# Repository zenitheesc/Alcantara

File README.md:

<h1 align="center" style="color:white; background-color:black">Alcantara</h1>
<h4 align="center"> Mobile Ground Station for stratospheric probe monitoring and rescue</h4>

<p align="center">

</p>

<p align="center">
    <a href="#environment-and-tools">Environment and Tools</a> •
    <a href="#Block-Diagram">Block Diagram</a> •
    <a href="#Schematic">Schematic</a> • 
    <a href="#Board">Board</a> • 
    <a href="#BOM">BOM</a> • 
    <a href="#Use-Concept">Use Concept</a>
</p>

The Alcantara board functions as a ground station and data hub for the probe flights .

It is equipped with a EBYTE E22-900M30S 30dB module that carries the Semtech SX1262 transceiver, capable of LoRa, (G)FSK and OOK. The packets received from the probe can then be sent via WiFi, Bluetooth or Serially to a host computer or mobile phone.

The onboard GNSS module carries the NEO-M8N from u-blox, enabling it to be used as a tracking device.

## Environment and tools

This system was designed using KiCad 5.1.10.

## Block Diagram

## Schematic

The design was separated in hierarchical sheets to accommodate all components in an orderly way.

On the experimental_realocate_components sheet you can find the ESP32 WROOM Module, the SD Card module (connected via SPI), Boot and Reset button (with the Brownout prevention voltage supervisor), auto upload transistors and the external connector.

The second page contains the power section, with the TPS61092 Boost Converter (with another voltage supervisor for undervolting protection for the battery) for 5V, a 3.3V linear voltage regulator, the battery with a P channel mosfet for reverse voltage protection and a MAX17201G+T stand-alone fuel gauge for the 18650 battery voltage and current monitoring.

On the third page you find the Neo-M8N module from u-blox and the E22-900M30S module from EBYTE.

And the last page has the peripherals, the USB connector with its ESD protector, the RGB LED, the buzzer with its mosfet, the two user interface buttons and the USB to Serial Converter.

## Board

## Interactive BOM

https://htmlpreview.github.io/?https://github.com/zenitheesc/Alcantara_v.1.0/blob/experimental_realocate_components/Other_Files/ibom.html

<!--
## Use concept

---

<p align="center">

</p>
<p align = "center">
<a href="zenith.eesc@gmail.com">zenith.eesc@gmail.com</a>
</p>
-->

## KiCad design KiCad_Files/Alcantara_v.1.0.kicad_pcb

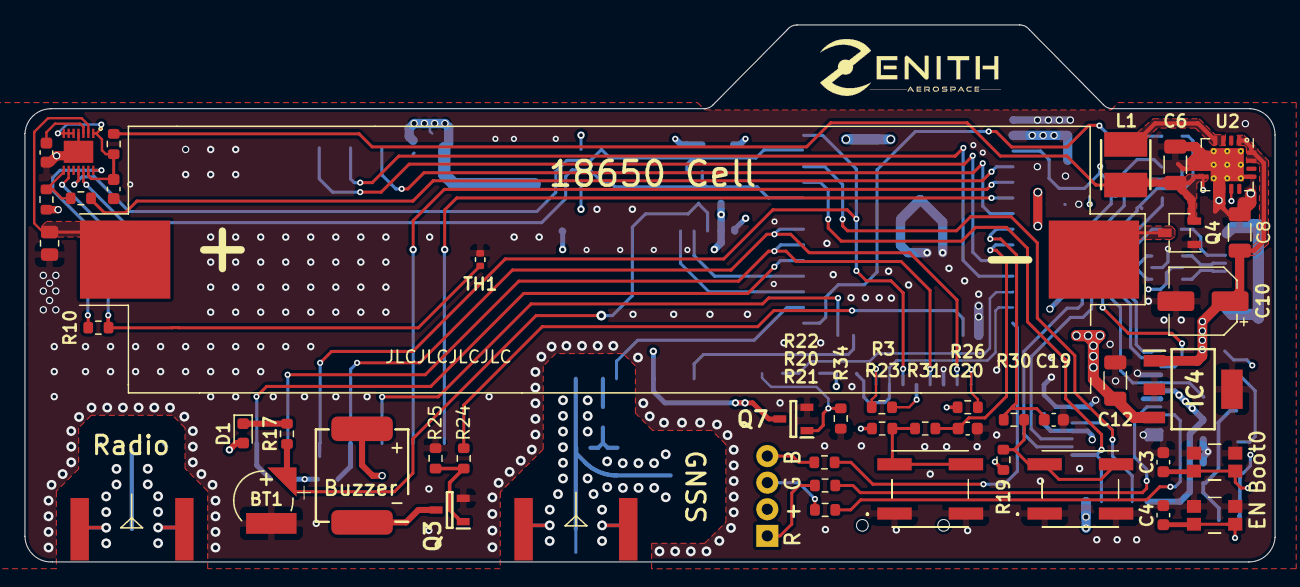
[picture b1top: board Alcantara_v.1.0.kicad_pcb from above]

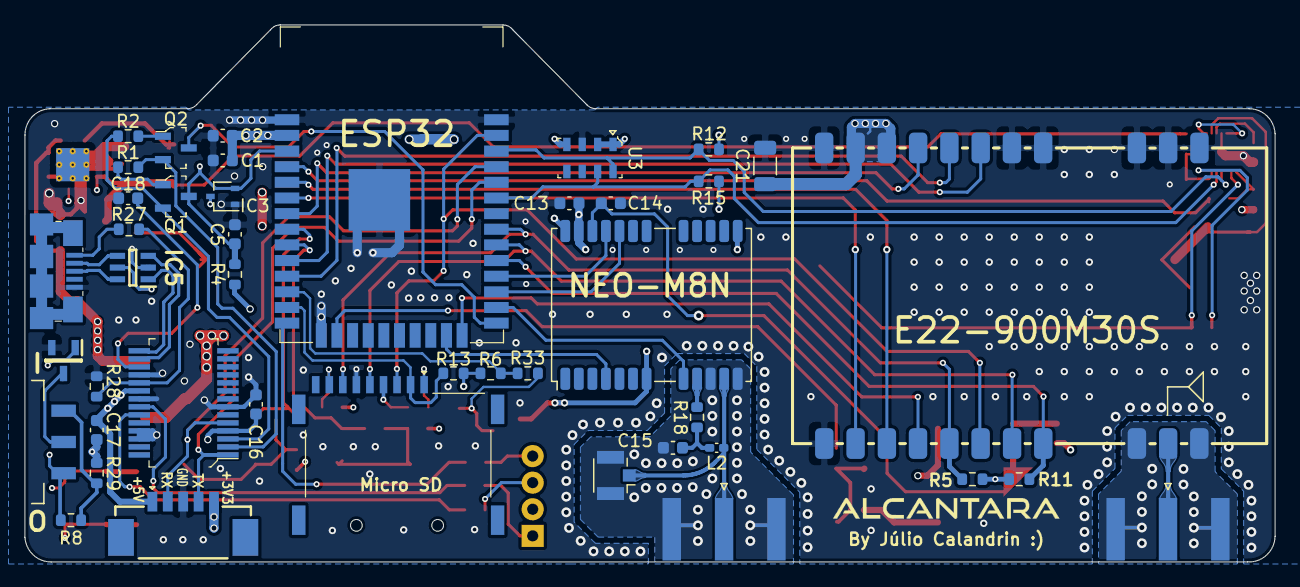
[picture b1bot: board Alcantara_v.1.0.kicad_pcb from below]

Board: 4 copper layers, 101.5 x 43.6 mm, 88 parts (43 on the bottom side), 74 nets.

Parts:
BT1: ML414H_IV01E; SEIKO_ML414H_IV01E
BT2: Battery_Cell; BatteryHolder_Keystone_1042_1x18650_Modified
C1, C3, C4, C9: 0.1uF; C_0603_1608Metric
C2, C5: 10uF; C_0603_1608Metric
C6, C12: 10uF; C_1206_3216Metric
C7: 0.47uF; C_0603_1608Metric
C8: 2.2uF; C_1206_3216Metric
C10: 100uF; CP_Elec_5x5.3
C13, C14, C19, C20: 1uF; C_0603_1608Metric
C15: 10nF; C_0603_1608Metric
C16, C17, C18: 100nF; C_0603_1608Metric
C21: 1uF; C_1206_3216Metric
D1: D_Schottky_Small; D_0603_1608Metric
D2: LED_RGBA; LED_D5.0mm-4_RGB_Wide_Pins
IC1: TLV809ED29DBZR; SOT95P237X112-3N
IC2: MAX17201G+T; SON40P300X300X80-15N
IC3: TLV803EA30DCKR; SOT-323_SC-70
IC4: TC1264-3.3VDB; SOT230P700X180-4N
IC5: PESD2ETH-ADX; SOT95P275X110-6N
J1: U_FL-R-SMT_10_; U.FL_Hirose_U.FL-R-SMT-1_Vertical
J2, J3: 142-0701-801; SMA_Amphenol_132289_EdgeMount
J4: USB_B_Micro; USB_Micro_B_Female_10118192
J5: MEM2075-00-140-01-A; MEM20750014001A
J8: 53261-0527; 532610527
L1: 6.8uH; INDPM4040X210N
L2: L_Small; L_0402_1005Metric_Pad0.77x0.64mm_HandSolder
MOD1: ESP32-WROOM-32; ESP32-WROOM-32D
Q1, Q2: MMSS8050-H-TP; SOT-23-3
Q3, Q7: 2N7002NXAKR; SOT95P230X110-3N
Q4: Q_PMOS_GSD; SOT346
R1, R2, R3, R4, R5, R6, R10, R11, R13, R19, R23, R25, R26, R28, R34: 10K; R_0603_1608Metric
R7: 0.01; R_0805_2012Metric
R8: 68k; R_0603_1608Metric
R9, R18: 10; R_0603_1608Metric
R12, R14, R15, R27: 4.7K; R_0603_1608Metric
R16, R20, R21, R22, R30, R31: 1K; R_0603_1608Metric
R17: 3.3K; R_0603_1608Metric
R24, R33: 330; R_0603_1608Metric
R29: 100k; R_0603_1608Metric
S1, S2: KSC941JLFS
S4, S5: EVP-AAM02W; EVPAAM02W
S6: MSS-102545-14A-V-SMT; SW_MSS-102545-14A-V-SMT
TH1: 10k; R_0402_1005Metric
U1: E22-900M30S
U2: TPS61092; Texas_S-PVQFN-N16_EP2.7x2.7mm_ThermalVias
U3: MS560702BA03-50; SMD-8_5x3mm
U4: NEO-M8N; ublox_NEO
U5: Buzzer_SMD_AST0760MCTRQ; AST0760MCTRQ
U7: FT232RL-REEL; SSOP-28_W5.30mm

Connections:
+3V3: C1.1, C2.1, C12.1, C13.1, C16.1, D1.2, D2.4, IC3.3, IC4.3, IC5.5, J5.P4, J8.5, MOD1.2, R3.1, R4.1, R5.1, R6.1, R11.2, R12.1, R13.2, R14.1, R15.1, R19.2, R23.2, R26.1, U3.1, U3.2, U3.4, U4.23, U7.4
+5V: C8.1, C10.1, C17.1, C21.1, IC4.1, J8.1, U1.9, U1.10, U2.1, U2.15, U2.16, U5.1, U7.20
/Power Management/Pack: C6.1, L1.2, Q4.2, R8.2, R9.2, S6.2, U2.8
BUTTON_1: C19.2, MOD1.8, R30.2
BUTTON_2: C20.2, MOD1.9, R31.2
BUZZER: MOD1.16, R24.1
EN: C4.1, C5.1, IC3.2, MOD1.3, Q1.3, R4.2, S4.A1, S4.B1
FTDI_DTR: Q2.2, R1.2, U7.2
FTDI_RTS: Q1.2, R2.2, U7.3
FTDI_RX: J8.2, MOD1.35, U7.5
FTDI_TX: J8.4, MOD1.34, U7.1
GAUGE_ALRT1: MOD1.4, R16.1
GAUGE_SCL: IC2.11, MOD1.36, R12.2, U3.8
GAUGE_SDA: IC2.12, MOD1.33, R15.2, U3.7
GND: BT1.2, C1.2, C2.2, C3.2, C4.2, C5.2, C6.2, C7.2, C8.2, C9.2, C10.2, C12.2, C13.2, C14.2, C16.2, C17.2, C18.1, C19.1, C20.1, C21.2, IC1.2, IC2.4, IC2.15, IC3.1, IC4.2, IC4.4, IC5.2, J4.5, J5.P6, J8.3, MOD1.1, MOD1.15, MOD1.38, MOD1.39, Q3.2, Q4.1, Q7.2, R7.1, R25.1, R28.2, R29.1, R34.1, S1.1, S1.2, S2.1, S2.2, S4.A2, S4.B2, S5.A2, S5.B2, TH1.2, U1.1, U1.2, U1.3, U1.4, U1.5, U1.11, U1.12, U2.5, U2.6, U2.7, U2.9, U2.10, U2.13, U2.17, U3.3, U7.7, U7.18, U7.21, U7.25, U7.26
GND1: Q7.3, U4.7, U4.13, U4.24
GNDA: C15.2, J1.2, J2.2, U4.10, U4.12
GPS_EXTINT: MOD1.23, U4.4
GPS_ON_OFF: MOD1.12, R6.2, R33.1
GPS_RESET: MOD1.26, U4.8
GPS_RX: MOD1.28, U4.21
GPS_TX: MOD1.27, U4.20
IO0: C3.1, MOD1.25, Q2.3, S5.A1, S5.B1
unnamed: BT1.1, C14.1, R17.1, U4.22
unnamed: BT2.1, Q4.3
unnamed: BT2.2, IC2.2, R7.2
unnamed: C7.1, IC2.3
unnamed: C9.1, IC2.1, IC2.5, IC2.6, IC2.7, IC2.13, R9.1
unnamed: C15.1, L2.1, R18.1
unnamed: C18.2, U7.17
unnamed: D1.1, R17.2
unnamed: D2.1, R20.1
unnamed: D2.2, R21.1
unnamed: D2.3, R22.1
unnamed: IC1.1, U2.11
unnamed: IC1.3, S6.1
unnamed: IC2.8, R14.2, R16.2
unnamed: IC2.9, R10.1, TH1.1
unnamed: IC2.14, R10.2
unnamed: J1.1, J2.1, L2.2, U4.11
unnamed: J3.1, U1.21
unnamed: J3.2, U1.20, U1.22
unnamed: J5.P1, R3.2
unnamed: J5.P8, R26.2
unnamed: L1.1, U2.3, U2.4
unnamed: Q1.1, R1.1
unnamed: Q2.1, R2.1
unnamed: Q3.1, R24.2, R25.2
unnamed: Q3.3, U5.2
unnamed: Q7.1, R33.2, R34.2
unnamed: R18.2, U4.9
unnamed: R19.1, R30.1, S1.3, S1.4
unnamed: R23.1, R31.1, S2.3, S2.4
unnamed: R27.2, R28.1, U7.19
unnamed: R8.1, R29.2, S6.3
RADIO_BUSY: MOD1.5, U1.14
RADIO_DIO1: MOD1.6, U1.13
RADIO_DIO2: MOD1.7, U1.8
RADIO_NRST: MOD1.24, U1.15
RADIO_NSS: MOD1.29, R11.1, U1.19
RADIO_RXEN: MOD1.10, U1.6
RADIO_TXEN: MOD1.11, U1.7
RGB_LED_B: MOD1.14, R22.2
RGB_LED_G: R21.2, U7.23
RGB_LED_R: R20.2, U7.22
SDCARD_NSS: J5.P2, MOD1.13, R13.1
USB_CONN_D+: IC5.6, J4.3
USB_CONN_D-: IC5.4, J4.2
USB_CONN_V+: J4.1, R27.1
USB_D+: IC5.1, U7.15
USB_D-: IC5.3, U7.16
VSPI_MISO: J5.P7, MOD1.31, R5.2, U1.16
VSPI_MOSI: J5.P3, MOD1.37, U1.17
VSPI_SCLK: J5.P5, MOD1.30, U1.18

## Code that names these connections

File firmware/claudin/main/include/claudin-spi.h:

#include "driver/spi_master.h"
#include "esp_log.h"

#define GPIO_RADIO_DIO_0 	26
#define GPIO_RADIO_DIO_1 	35

#define GPIO_RADIO_NRST 	16

#define GPIO_RADIO_SS 		18
#define VSPI_MISO 		19
#define VSPI_MOSI 		27 
#define VSPI_SCLK 		5

static const char *spi = "spi";

esp_err_t spi_add_device(spi_device_handle_t* spi_bus, uint32_t spi_clk);
esp_err_t spi_init();
esp_err_t spi_read_buffer(spi_device_handle_t spi_bus,uint8_t reg_addr,uint8_t* pvalue,uint16_t len);
esp_err_t spi_read_register(spi_device_handle_t spi_bus,uint8_t reg_addr,uint8_t* pvalue);
esp_err_t spi_write_buffer(spi_device_handle_t spi_bus,uint8_t reg_addr,uint8_t* pvalue,uint16_t len);
esp_err_t spi_write_register(spi_device_handle_t spi_bus,uint8_t reg_addr,uint8_t pvalue);
esp_err_t test_register(spi_device_handle_t spi_bus);

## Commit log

2021-09-02 Updated silk screens and components 3D models
2022-01-16 Updated RF section ground planes.
2022-01-16 Deleting excess files
2022-01-16 Origanized Folders
2022-01-17 Added Images
2022-01-17 Renamed Files
2022-01-17 Added Block Diagram
2022-01-20 Add shapes 3D folder
    Now all 3D models for the components are stored in a single folder, thanks to the Archive Plugin from https://github.com/MitjaNemec/Kicad_action_plugins.git
2022-01-20 Update PCB 3D shape file paths
2022-01-26 README: Delete duplicated header
2022-02-20 Realocated and replaced components
    Components where replaced because of the chip shortage, such as the 3.3 V Voltage regulator, the USB ESD protector and the SD Card holder.
    The ESP32 has been rotated and moved closer to the center of the board, now having it's antenna positioned outside of the original board outline, providing better range for the Bluetooth and Wi-Fi.
2022-02-23 Reduces board length to 101,5 mm
    JLC PCB allows a 4 layer PCB to be manufactured for just $8,00 if it is within 102 x 102 mm. The previous version was 105,47 mm, making it cost $37,00.
    To reduce the manufacturing cost the board had its size cut down to 101,5 mm. This was possible by moving the buzzer from the top left corner of the board to the free space between the two SMA connec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
2022-02-23 Update README.md
    Update board renders
2022-02-23 Archive 3D Models
2022-03-29 #3 - Create a 'Hello World' program via serial
2022-04-05 #3 - Fix project directory
2022-05-23 #3 - Create Alcantara's setup code
2022-05-24 #3 - Join all the RGB LED blink functions in only one fuction
2022-05-24 #3 - Change enums elements names; add suffixes in the typedefs; change uppercase names that aren't constant values
2022-05-30 #3 - Improve visibility of some commented lines
2022-05-30 #3 - Change the initialization of the timer pointer from NULL to nullptr
2022-06-02 #3 - Shorten the initialization of the radio_state array using Designated Initializers
2022-06-02 #3 - Include 'g_' prefix in all the global variables names
2022-06-09 Change radio's decoupling capacitor to the 1206 packaging size.
    Upgrades the radios capacitor and rerouted it's traces to better accommodate grounding vias.
2022-07-10 #4 - Implement configuration for using SD card
2022-07-14 Add MS5607 barometer.
    Adds MS5607 barometer and reorganized silkscreen.
2023-02-08 Update fp-info-cache
2023-06-26 #4 - Create radio parse funcions
2023-06-26 #4 - Add SDCard write, append and error handler functions
2023-09-19 added claudin files
2023-09-19 doc fix
2023-09-29 #9 - Implement FreeRTOS
2023-10-11 Code documented and SD removed
2023-10-11 Code improved
2023-10-16 nothing
2023-10-19 #9 - Create the data_massage string for each parse function, fix some text outputs, and implement exit if queue can't be created
2023-10-24 First version ESP-IDF
